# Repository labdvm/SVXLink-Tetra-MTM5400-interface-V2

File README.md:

# SVXLink-Tetra-MTM5400-interface-V2
SVXLink-Tetra dedicated interface with integrated FT232RL for MTM5400 and USB audio card.
This is dedicated inteface for Motorola MTM5400 and USB Audio card CM108 and others.
V2.1.
Z32IT

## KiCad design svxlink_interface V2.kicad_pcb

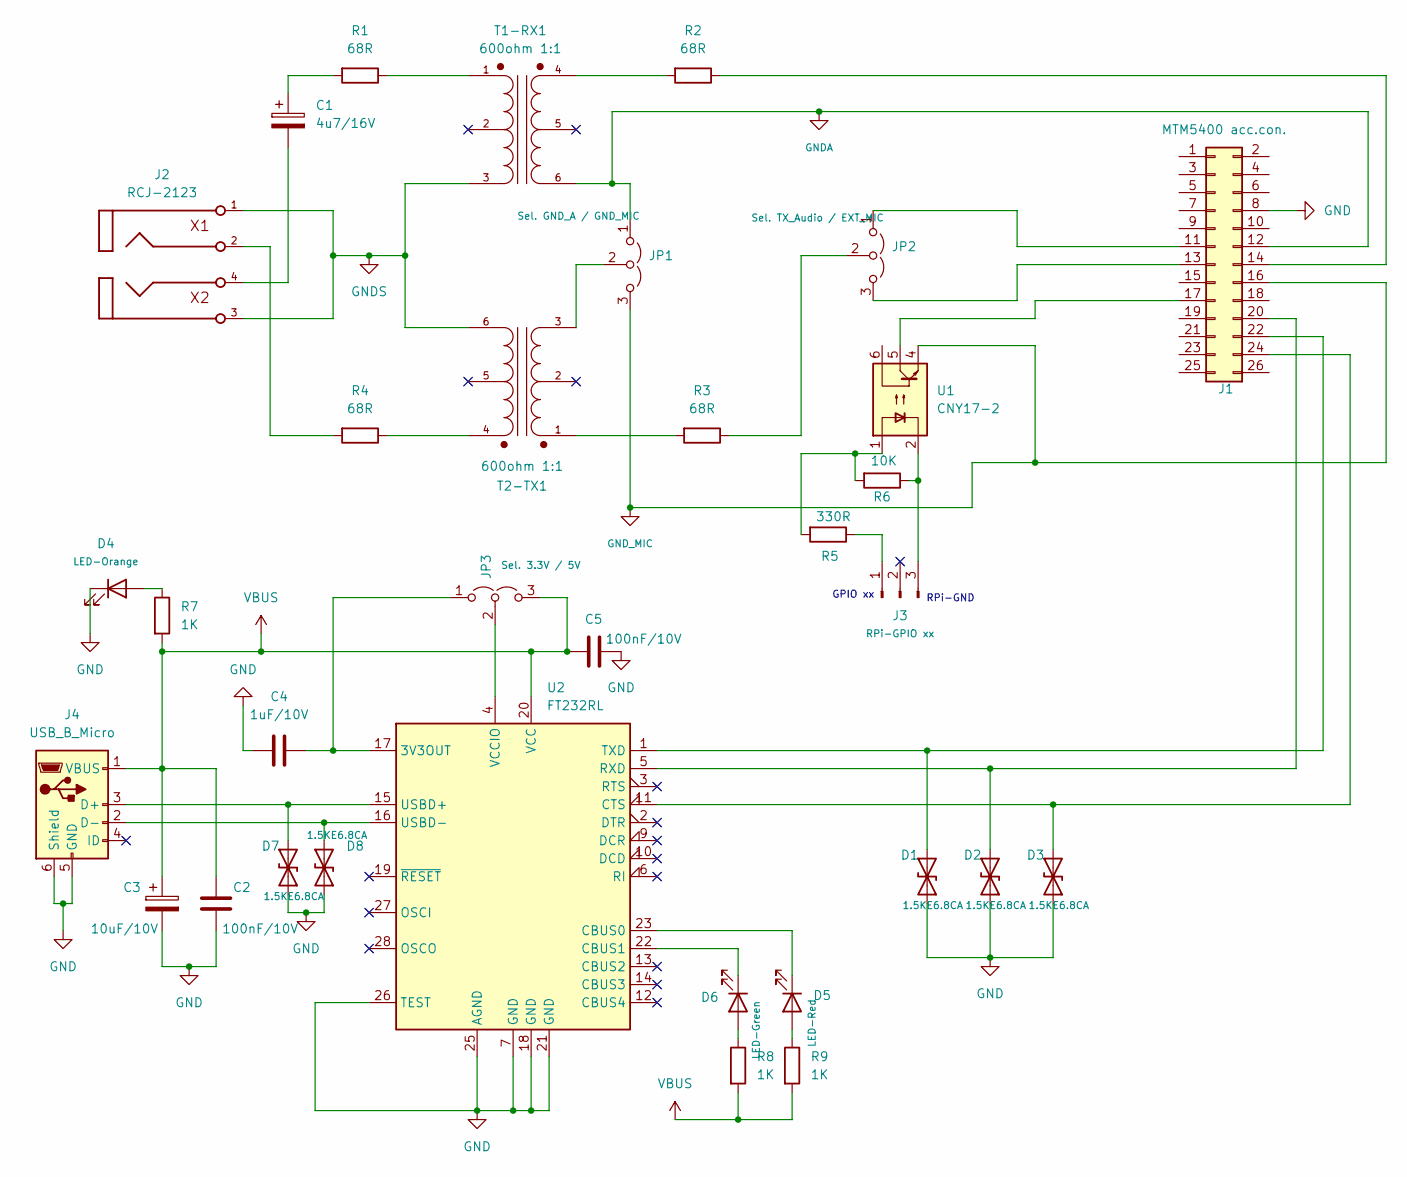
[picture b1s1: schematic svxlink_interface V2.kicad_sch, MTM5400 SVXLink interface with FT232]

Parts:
C1: 4u7/16V; CP_Radial_D4.0mm_P2.00mm
C2, C5: 100nF/10V; C_1210_3225Metric_Pad1.33x2.70mm_HandSolder
C3: 10uF/10V; CP_EIA-2012-12_Kemet-R_Pad1.30x1.05mm_HandSolder
C4: 1uF/10V; C_1210_3225Metric_Pad1.33x2.70mm_HandSolder
D1, D2, D3, D7, D8: 1.5KE6.8CA; D_DO-201AE_P15.24mm_Horizontal
D4: LED-Orange; LED_1206_3216Metric_Pad1.42x1.75mm_HandSolder
D5: LED-Red; LED_1206_3216Metric_Pad1.42x1.75mm_HandSolder
D6: LED-Green; LED_1206_3216Metric_Pad1.42x1.75mm_HandSolder
J1: MTM5400 acc.con.; MTM5400_1
J2: RCJ-2123; RCJ-2121
J3: RPi-GPIO xx; PinHeader_1x03_P2.54mm_Vertical
J4: USB_B_Micro; USB_Micro-B_Molex-105017-0001
JP1: Sel. GND_A / GND_MIC; PinHeader_1x03_P2.54mm_Vertical
JP2: Sel. TX_Audio / EXT_MIC; PinHeader_1x03_P2.54mm_Vertical
JP3: Sel. 3.3V / 5V; PinHeader_1x03_P2.54mm_Vertical
R1, R2, R3, R4: 68R; R_Axial_DIN0207_L6.3mm_D2.5mm_P10.16mm_Horizontal
R5: 330R; R_Axial_DIN0207_L6.3mm_D2.5mm_P10.16mm_Horizontal
R6: 10K; R_Axial_DIN0207_L6.3mm_D2.5mm_P10.16mm_Horizontal
R7, R8, R9: 1K; R_1206_3216Metric_Pad1.30x1.75mm_HandSolder
T1-RX1, T2-TX1: 600ohm 1:1; XFMR_TY-145P; PARTREV 2016
U1: CNY17-2; DIP-6_W7.62mm_Socket
U2: FT232RL; SSOP-28_5.3x10.2mm_P0.65mm

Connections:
GND: C2.2, C3.2, C4.1, C5.2, D1.1 (A1), D2.1 (A1), D3.1 (A1), D4.1 (K), D7.1 (A1), D8.1 (A1), J1.8 (GND), J4.5 (GND), J4.6 (Shield), U2.7 (GND), U2.18 (GND), U2.21 (GND), U2.25 (AGND), U2.26 (TEST)
GNDA: J1.12 (GND_A), JP1.1 (A), T1-RX1.6
GNDS: J2.1, J2.3, T1-RX1.3, T2-TX1.6
GND_MIC: J1.16 (GND_MIC), JP1.3 (B), U1.4
unnamed: C1.1, R1.2
unnamed: C1.2, J2.4
unnamed: D1.2 (A2), J1.22 (RXD), U2.1 (TXD)
unnamed: D2.2 (A2), J1.20 (TXD), U2.5 (RXD)
unnamed: D3.2 (A2), J1.24 (CTS), U2.11 (CTS)
unnamed: D4.2 (A), R7.1
unnamed: D5.2 (A), R9.1
unnamed: D5.1 (K), U2.23 (CBUS0)
unnamed: D6.2 (A), R8.1
unnamed: D6.1 (K), U2.22 (CBUS1)
unnamed: D7.2 (A2), J4.3 (D+), U2.15 (USBD+)
unnamed: D8.2 (A2), J4.2 (D-), U2.16 (USBD-)
unnamed: J1.13 (EXT_MIC), JP2.3 (B)
unnamed: J1.17 (PTT), U1.5
unnamed: J1.14 (RX_Audio), R2.1
unnamed: J1.11 (TX_Audio), JP2.1 (A)
unnamed: J2.2, R4.2
unnamed: J3.1, R5.1
unnamed: J3.3, R6.1, U1.2
unnamed: JP1.2 (C), T2-TX1.3
unnamed: JP2.2 (C), R3.1
unnamed: C4.2, JP3.1 (A), U2.17 (3V3OUT)
unnamed: JP3.2 (C), U2.4 (VCCIO)
unnamed: R1.1, T1-RX1.1
unnamed: R2.2, T1-RX1.4
unnamed: R3.2, T2-TX1.1
unnamed: R4.1, T2-TX1.4
unnamed: R5.2, R6.2, U1.1
VBUS: C2.1, C3.1, C5.1, J4.1 (VBUS), JP3.3 (B), R7.2, R8.2, R9.2, U2.20 (VCC)

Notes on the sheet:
RPi-GND
GPIO xx

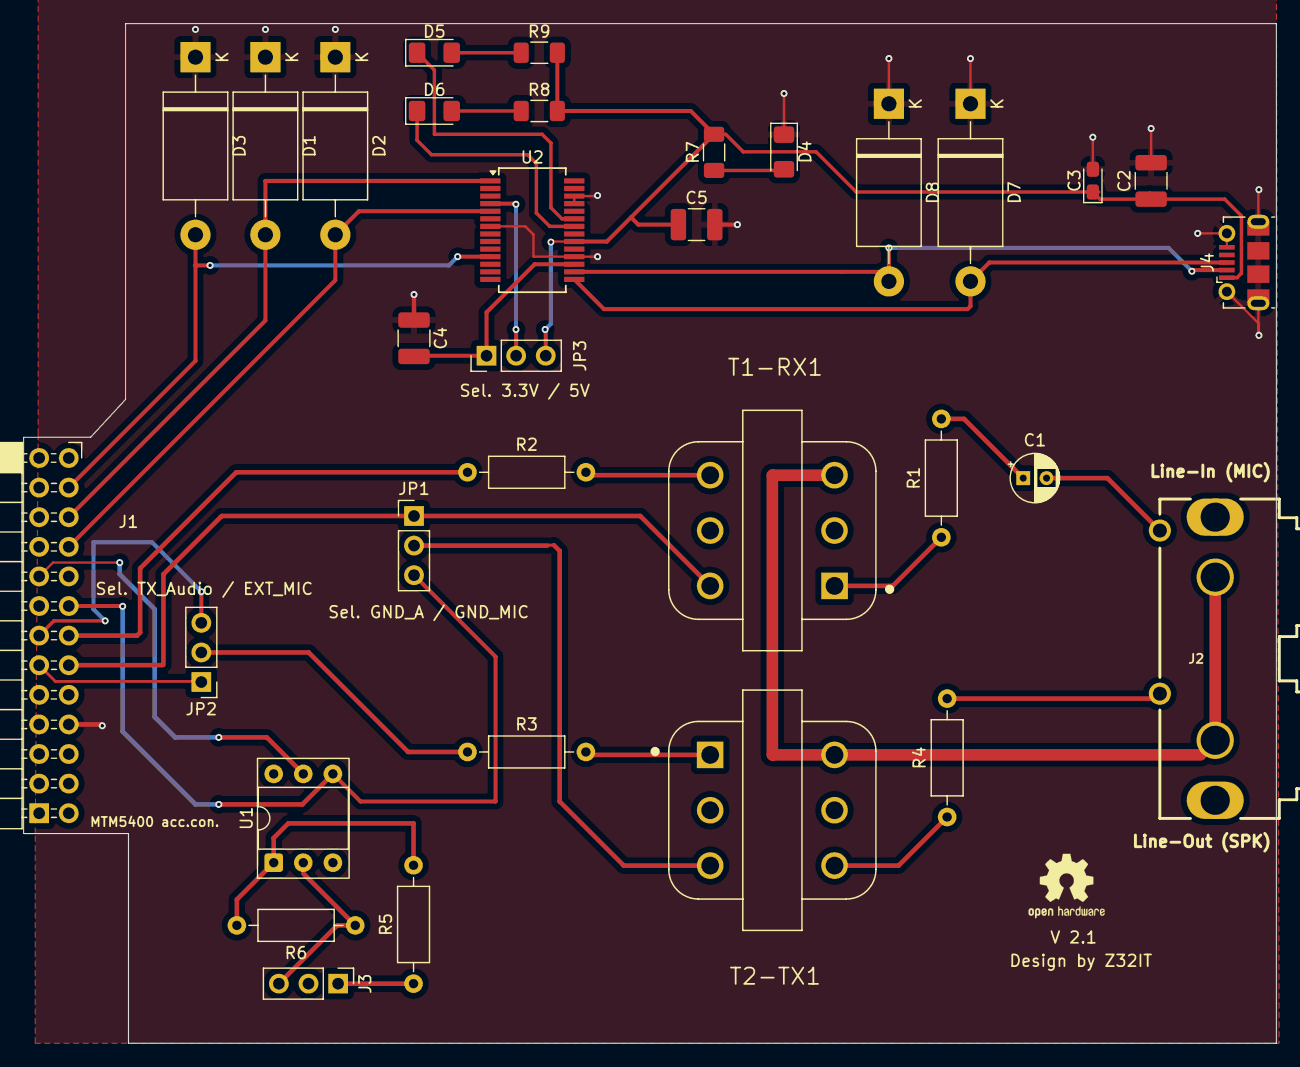
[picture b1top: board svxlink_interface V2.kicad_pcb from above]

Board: 2 copper layers, 107.5 x 87.5 mm, 33 parts (0 on the bottom side), 33 nets.

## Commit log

2026-01-03 Update README to include FT232RL integration
